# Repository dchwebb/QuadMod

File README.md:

# Quadmod

Quadmod
--------

Quadmod is a Eurorack modular four channel effect module. A modulation section allows either phasing or flanging followed by a delay. As part of the Mountjoy Modular polyphonic range the module uses a series of intermodulation paths to convert a four channel input to a stereo output.

### Phaser
The phaser uses 4 (configurable up to 16) all pass filters to create the phasing effect. Each channel's all pass filter is 45° out of phase with the last. The regeneration (feedback) control progressively mixes one channel to the next to widen the stereo spectrum.

### Flanger
The flanger uses multiple short modulated delays to create a flanger/chorus effect. The delay times are modulated with a 45° phase shift from channel to channel. A wide option (on by default) mixes a further 180° phase shifted version of each channel's signal to the next channel.

Technical
---------

Quadmod uses an STM32563 microcontroller which controls a four channel Audio Codec (AsahiKasei AK4619) using SPI for configuration and SAI (Serial Ausio Interface) peripheral to manage the 4 in and 4 out I2S audio streams. The microcontroller reads the front panel controls with internal 12 bit ADCs.

A USB socket is provided for serial configuration and a web editor using WebSerial provides a UI for editing settings. Three LEDs are controlled with PWM from the MCU to indicate modulation LFO rates and delay times.

Construction is a sandwich of three PCBs with a component board, a controls board and a panel. PCBs designed in Kicad v7.

[Components schematic](https://raw.githubusercontent.com/dchwebb/Quadmod/master/Hardware/Quadmod_Components.pdf)

[Controls schematic](https://raw.githubusercontent.com/dchwebb/Quadmod/master/Hardware/Quadmod_Controls.pdf)

In addition the the Eurorack +/-12V rails (which have polarity protection and filtering) a digital 3.3v rail is supplied using a TI TPS561201 and analog 3.3v is generated with an LM1117-3.3.

Errata
------

Version 1 of the component PCB had microcontroller pins PC0 (SAI2_SD_A) and PC1 (DLY_TIME_POT) flipped.

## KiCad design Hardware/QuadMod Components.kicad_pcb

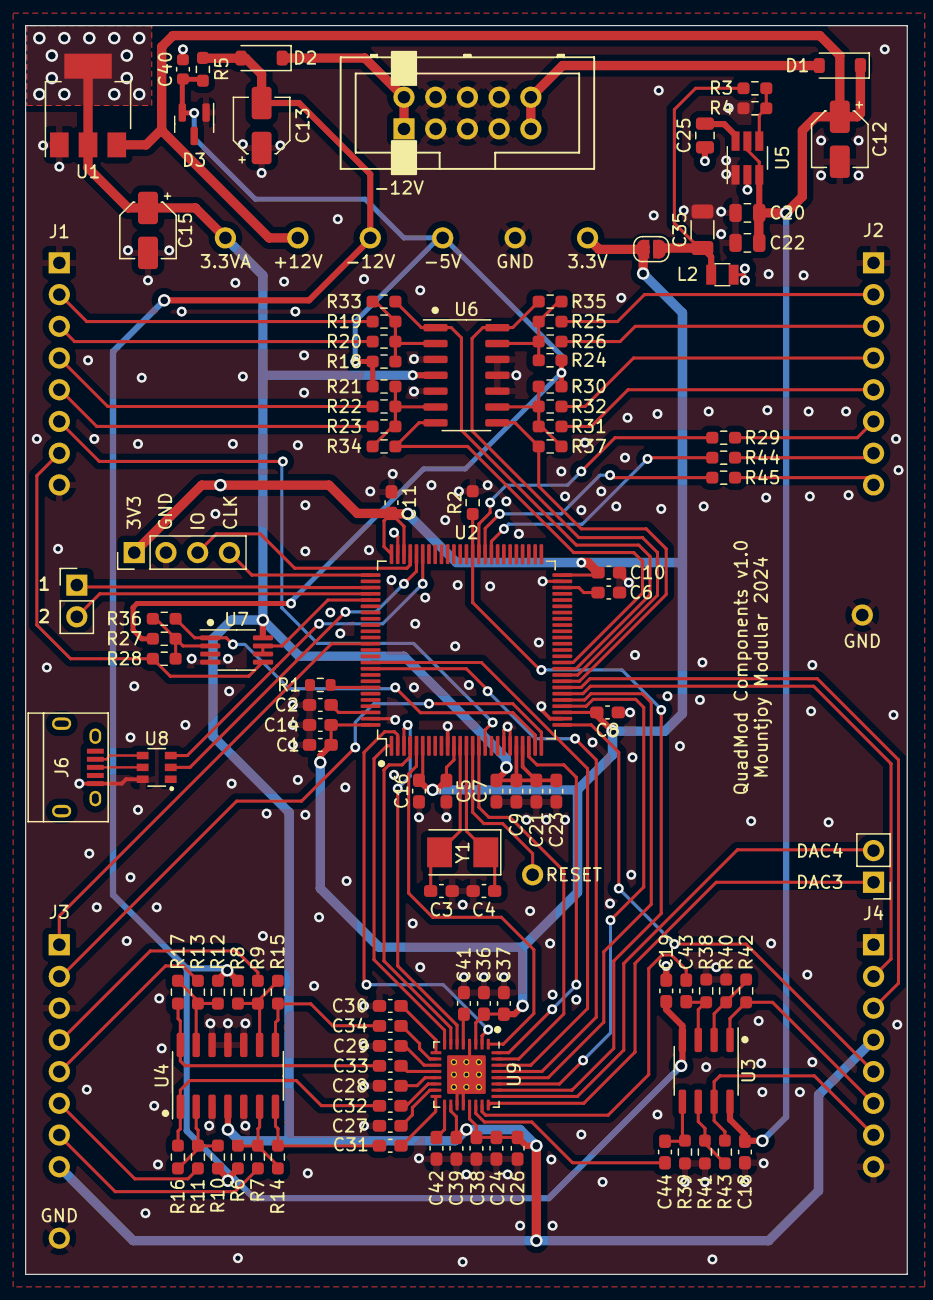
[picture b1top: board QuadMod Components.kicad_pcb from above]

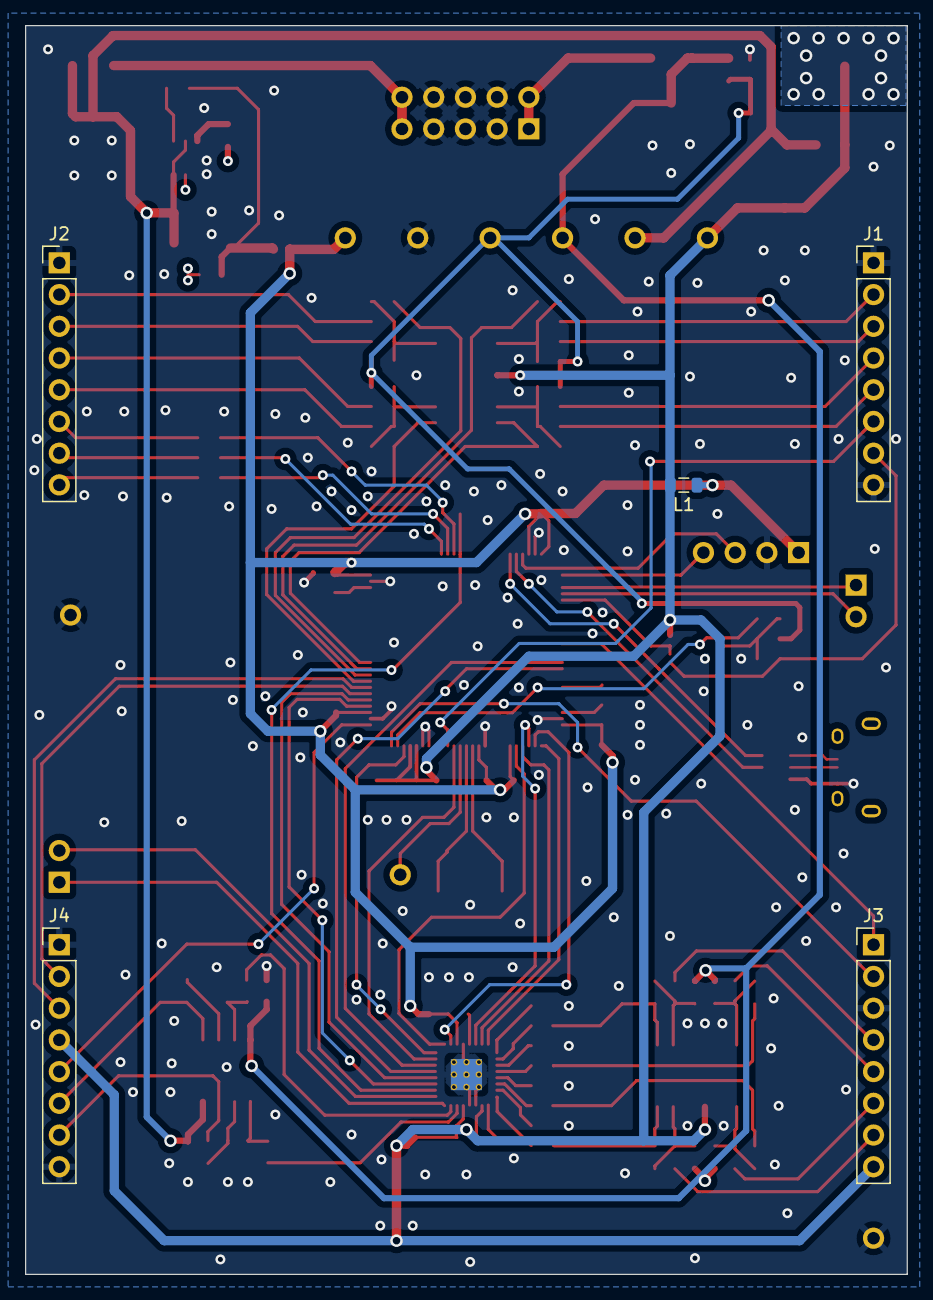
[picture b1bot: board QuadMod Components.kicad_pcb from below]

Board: 4 copper layers, 70.6 x 100.0 mm, 122 parts (5 on the bottom side), 102 nets.

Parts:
C1: 4.7uF; C_0603_1608Metric_Pad1.08x0.95mm_HandSolder
C2, C6, C41, C42: 2.2uF; C_0603_1608Metric_Pad1.08x0.95mm_HandSolder
C3, C4: 30pF; C_0603_1608Metric_Pad1.08x0.95mm_HandSolder
C5, C8, C9, C10, C11, C14, C16, C18, C19, C21, C24, C37, C38: 100nF; C_0603_1608Metric_Pad1.08x0.95mm_HandSolder
C7, C23, C27, C28, C29, C30, C31, C32, C33, C34, C43, C44: 1uF; C_0603_1608Metric_Pad1.08x0.95mm_HandSolder
C12: 47uF; CP_Elec_4x5.8
C13, C15: 22uF; CP_Elec_4x5.8
C20, C22: 10uF; C_0805_2012Metric
C25: 100nF; C_0805_2012Metric
C26, C36, C39: 10uF; C_0603_1608Metric_Pad1.08x0.95mm_HandSolder
C35: 47uF; R_1206_3216Metric
C40: 100nF; C_0603_1608Metric
D1, D2: 1N5819; D_SOD-123
D3: LM4040DBZ-5; SOT-23
J1, J2, J3, J4: Conn_01x08_Pin; PinHeader_1x08_P2.54mm_Vertical
J5: Eurorack_10_pin_power; Eurorack_10_pin_header
J6: USB_B_Micro; USB_Micro-B_Amphenol
J7: Prog_Header; PinHeader_1x04_P2.54mm_Vertical
J8: Extra_Outs; PinHeader_1x02_P2.54mm_Vertical
J9: Test_Outs; PinHeader_1x02_P2.54mm_Vertical
JP2: Jumper; SolderJumper-2_P1.3mm_Open_RoundedPad1.0x1.5mm
L1: L; L_0805_2012Metric
L2: 3.3uH; L_0806
R1: 100k; R_0603_1608Metric
R2, R4, R40, R41: 10k; R_0603_1608Metric_Pad0.98x0.95mm_HandSolder
R3: 33k; R_0603_1608Metric_Pad0.98x0.95mm_HandSolder
R5: 2k2; R_0603_1608Metric_Pad0.98x0.95mm_HandSolder
R6, R8, R10, R12: 100k; R_0603_1608Metric_Pad0.98x0.95mm_HandSolder
R7, R9, R11, R13: 68k; R_0603_1608Metric_Pad0.98x0.95mm_HandSolder
R14, R15, R16, R17, R42, R43: 14k; R_0603_1608Metric_Pad0.98x0.95mm_HandSolder
R18, R21, R24, R27, R30: 75k; R_0603_1608Metric_Pad0.98x0.95mm_HandSolder
R19, R22, R25, R28, R31: 91k; R_0603_1608Metric_Pad0.98x0.95mm_HandSolder
R20, R23, R26, R32, R33, R34, R35, R36, R37: 47k; R_0603_1608Metric_Pad0.98x0.95mm_HandSolder
R29, R44, R45: 1k; R_0603_1608Metric_Pad0.98x0.95mm_HandSolder
R38, R39: 390k; R_0603_1608Metric_Pad0.98x0.95mm_HandSolder
TP1, TP2, TP3, TP4, TP5, TP6, TP7, TP9: TestPoint; 1mm_Test_Point
TP8: Reset; 1mm_Test_Point
U1: LD1117-3.3-4Tab; SOT-223-3_TabPin2
U2: STM32H563VIT; LQFP-100_14x14mm_P0.5mm
U3: TL072; SOIC-8_3.9x4.9mm_P1.27mm
U4, U6: MCP6004; SO-14_3.9x8.65mm_P1.27mm
U5: TPS561201; SOT-23-6_Handsoldering
U7: MCP6002-xSN; MSOP-8_3x3mm_P0.65mm
U8: STF202-22T1G
U9: AK4619VN; QFN-32-1EP_5x5mm_P0.5mm_EP3.1x3.1mm_ThermalVias
Y1: 8MHz 20pF; Crystal_SMD_5032-2Pin_5.0x3.2mm

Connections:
+3.3V: C1.2, C5.2, C8.2, C10.2, C11.2, C14.2, C16.2, C36.2, C37.2, J7.1, JP2.2 (B), L1.1, TP5.1, U2.6 (VBAT), U2.11 (VDD), U2.28 (VDD), U2.50 (VDD), U2.73 (VDDUSB), U2.75 (VDD), U2.100 (VDD), U9.3 (TVDD)
+3.3VA: C7.2, C9.2, C15.1, C21.2, C23.2, C24.2, C26.2, C38.2, C39.2, J3.8, J4.4, L1.2, TP4.1, U1.2 (VO), U2.21 (VREF+), U2.22 (VDDA), U4.4 (V+), U6.4 (V+), U7.8 (V+), U9.18 (AVDD), U9.21 (VREFH)
+12V: C12.1, C18.2, C20.1, C22.1, D1.1 (K), TP2.1, U1.3 (VI), U3.8 (V+), U5.3 (VIN), U5.5 (EN)
-12V: C13.2, C19.2, D2.2 (A), R5.1, R6.2, R8.2, R10.2, R12.2, TP3.1, U3.4 (V-)
/+12V_IN: D1.2 (A), J5.9, J5.10
/-5V_REF: C40.2, D3.2 (A), R5.2, R18.2, R21.2, R24.2, R27.2, R30.2, TP1.1
/-12V_IN: D2.1 (K), J5.1, J5.2
/Audio_In1: C31.2, R14.1, U4.7
/Audio_In2: C32.2, R16.1, U4.1
/Audio_In3: C33.2, R17.1, U4.14
/Audio_In4: C34.2, R15.1, U4.8
/Audio_Out1: C44.2, U9.22 (AOUT1L)
/Audio_Out2: C43.2, U9.23 (AOUT1R)
/Audio_Out3: J8.1, U9.24 (AOUT2L)
/Audio_Out4: J8.2, U9.25 (AOUT2R)
/CB: C25.2, U5.6 (VBST)
/CLOCKED_LED: J2.6, R29.2
/Clock_Scaled: U2.80 (PC12), U7.6 (-), U7.7
/Clocked_Led_Out: R29.1, U2.61 (PD14)
/D3V3: C35.1, JP2.1 (A), L2.2, R3.1
/D+: J6.3 (D+), U8.5 (D1_IN)
/D-: J6.2 (D-), U8.4 (D2_IN)
/DELAY_LED: J2.7, R44.2
/DLY_FEEDBACK: J3.2, U2.25 (PA2)
/DLY_FILTER_CV: J1.4, R22.2
/DLY_FILTER_POT: J1.5, R23.2
/DLY_MIX: J4.3, U2.32 (PA7)
/DLY_TIME_CV: J1.7, R28.2, U7.5 (+)
/DLY_TIME_POT: J1.6, U2.16 (PC1)
/Delay_Filter: R34.1, U2.36 (PB1), U6.7
/Delay_Led_Out: R44.1, U2.59 (PD12)
/Delay_Time: R36.1, U2.24 (PA1), U7.1
/FB: R3.2, R4.1, U5.4 (VFB)
/FX_FEEDBACK_CV: J2.2, R25.2
/FX_FEEDBACK_POT: J2.3, R26.2
/FX_Feedback: R35.1, U2.34 (PC5), U6.14
/FX_LED: J2.8, R45.2
/FX_Led_Out: R45.1, U2.60 (PD13)
/FX_MIX: J4.5, U2.26 (PA3)
/FX_TYPE: J3.1, U2.87 (PD6)
/IN1: J3.7, R7.2
/IN2: J3.6, R11.2
/IN3: J3.5, R13.2
/IN4: J3.4, R9.2
/LFO_BASEFREQ_CV: J1.2, R19.2
/LFO_BASEFREQ_POT: J1.3, R20.2
/LFO_Base_Freq: R33.1, U2.35 (PB0), U6.1
/LFO_RANGE: J4.2, U2.31 (PA6)
/LFO_SPEED_CV: J2.5, R31.2
/LFO_SPEED_POT: J2.4, R32.2
/LFO_Speed: R37.1, U2.33 (PC4), U6.8
/OUT_AMP1: J4.7, R43.1, U3.7
/OUT_AMP2: J4.6, R42.1, U3.1
/PDN: R2.1, U2.62 (PD15), U9.26 (PDN)
/SAI1_FS_A: U2.3 (PE4), U9.6 (LRCK)
/SAI1_MCLK_A: U2.1 (PE2), U9.8 (MCLK)
/SAI1_SCK_A: U2.4 (PE5), U9.7 (BICK)
/SAI1_SD_A: U2.5 (PE6), U9.1 (SDIN1)
/SAI1_SD_B: U2.2 (PE3), U9.2 (SDIN2)
/SAI2_SD_A: U2.15 (PC0), U9.31 (SDOUT1)
/SAI2_SD_B: U2.23 (PA0), U9.32 (SDOUT2)
/SPI1_MISO: U2.90 (PB4), U9.30 (SDA/SO)
/SPI1_MOSI: U2.91 (PB5), U9.29 (SI)
/SPI1_NSS: U2.29 (PA4), U9.27 (CAD/~CS)
/SPI1_SCK: U2.30 (PA5), U9.28 (SCL/SCLK)
/SWCLK: J7.4, U2.76 (PA14)
/SWIO: J7.3, U2.72 (PA13)
/Test_Out1: J9.1, U2.78 (PC10)
/Test_Out2: J9.2, U2.79 (PC11)
/USB_DM: U2.70 (PA11), U8.3 (D2_OUT)
/USB_DP: U2.71 (PA12), U8.2 (D1_OUT)
/VSW: C25.1, L2.1, U5.2 (SW)
GND: C1.1, C2.2, C3.2, C4.2, C5.1, C6.2, C7.1, C8.1, C9.1, C10.1, C11.1, C12.2, C13.1, C14.1, C15.2, C16.1, C18.1, C19.1, C20.2, C21.1, C22.2, C23.1, C24.1, C26.1, C27.2, C28.2, C29.2, C30.2, C35.2, C36.1, C37.1, C38.1, C39.1, C40.1, C41.2, C42.2, D3.1 (K), J1.1, J1.8, J2.1, J3.3, J4.1, J4.8, J5.3, J5.4, J5.5, J5.6, J5.7, J5.8, J6.5 (GND), J7.2, R1.1, R2.2, R4.2, R38.2, R39.2, R40.2, R41.2, TP6.1, TP7.1, TP9.1, U1.1 (GND), U2.10 (VSS), U2.19 (VSSA), U2.20 (VREF-), U2.27 (VSS), U2.49 (VSS), U2.74 (VSS), U2.99 (VSS), U4.3 (+), U4.5 (+), U4.10 (+), U4.11 (V-), U4.12 (+), U5.1 (GND), U6.3 (+), U6.5 (+), U6.10 (+), U6.11 (V-), U6.12 (+), U7.3 (+), U7.4 (V-), U8.6 (GND), U9.4 (VSS2), U9.19 (VSS1), U9.20 (VREFL), U9.33 (PAD)
unnamed: C2.1, U2.98 (VCAP)
unnamed: C6.1, U2.48 (VCAP)
unnamed: R1.2, U2.94 (BOOT0)
unnamed: TP8.1, U2.14 (NRST)
unnamed: C3.1, U2.12 (PH0), Y1.2
unnamed: C4.1, U2.13 (PH1), Y1.1
unnamed: C43.1, R38.1, U3.3 (+)
unnamed: R40.1, R42.2, U3.2 (-)
unnamed: C44.1, R39.1, U3.5 (+)
unnamed: R41.1, R43.2, U3.6 (-)
unnamed: R10.1, R11.1, R16.2, U4.2 (-)
unnamed: R6.1, R7.1, R14.2, U4.6 (-)
unnamed: R8.1, R9.1, R15.2, U4.9 (-)
unnamed: R12.1, R13.1, R17.2, U4.13 (-)
unnamed: R18.1, R19.1, R20.1, R33.2, U6.2 (-)
unnamed: R21.1, R22.1, R23.1, R34.2, U6.6 (-)
unnamed: R30.1, R31.1, R32.1, R37.2, U6.9 (-)
unnamed: R24.1, R25.1, R26.1, R35.2, U6.13 (-)
unnamed: R27.1, R28.1, R36.2, U7.2 (-)
unnamed: C41.1, U9.5 (AVDRV)
unnamed: C27.1, U9.15 (IN1N/AIN2L/GND3L)
unnamed: C31.1, U9.16 (IN1P/AIN1L/AIN3L)
unnamed: C28.1, U9.13 (IN2N/AIN2R/GND3R)
unnamed: C32.1, U9.14 (IN2P/AIN1R/AIN3R)
unnamed: C29.1, U9.11 (IN3N/AIN5L/GND6L)
unnamed: C33.1, U9.12 (IN3P/AIN4L/AIN6L)
unnamed: C30.1, U9.9 (IN4N/AIN5R/GND6R)
unnamed: C34.1, U9.10 (IN4P/AIN4R/AIN6R)
unnamed: C42.1, U9.17 (VCOM)

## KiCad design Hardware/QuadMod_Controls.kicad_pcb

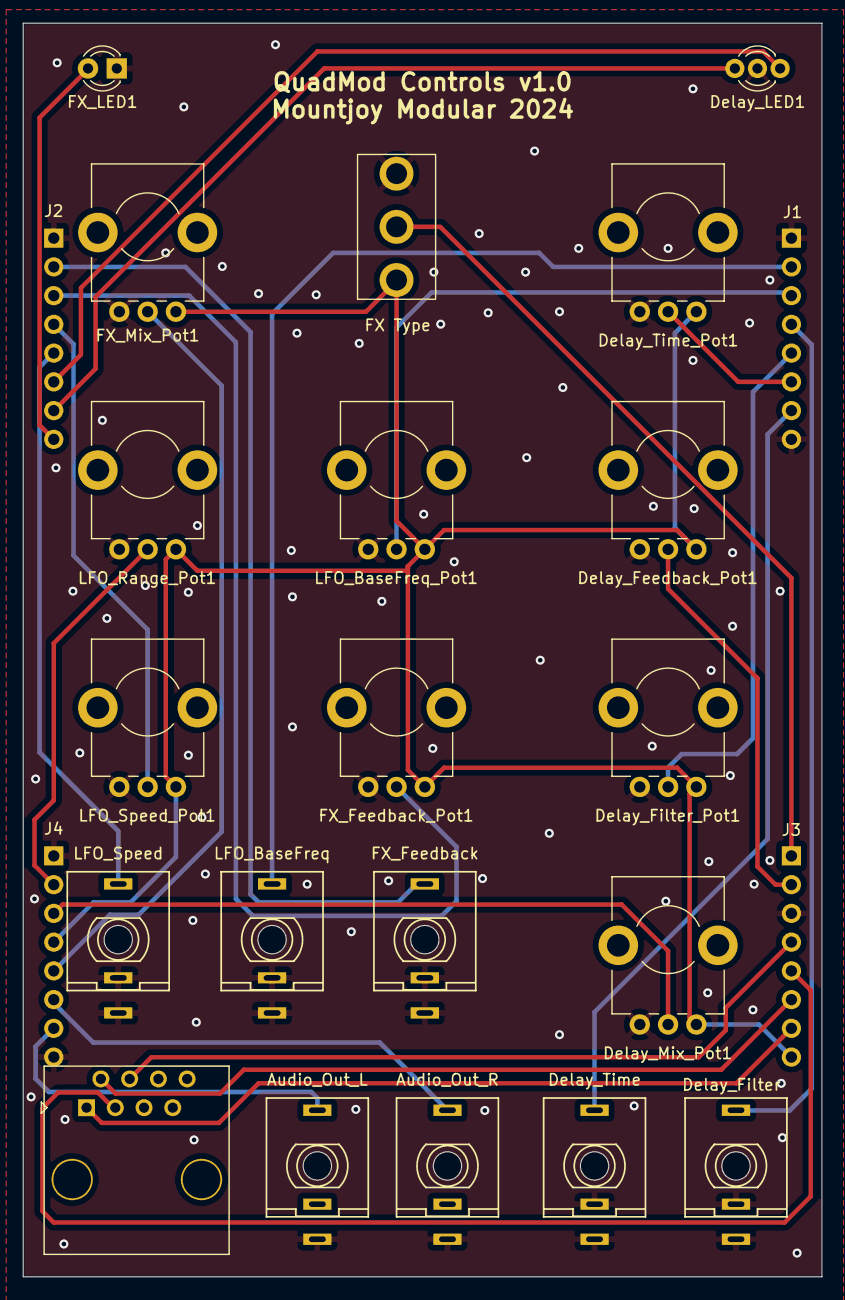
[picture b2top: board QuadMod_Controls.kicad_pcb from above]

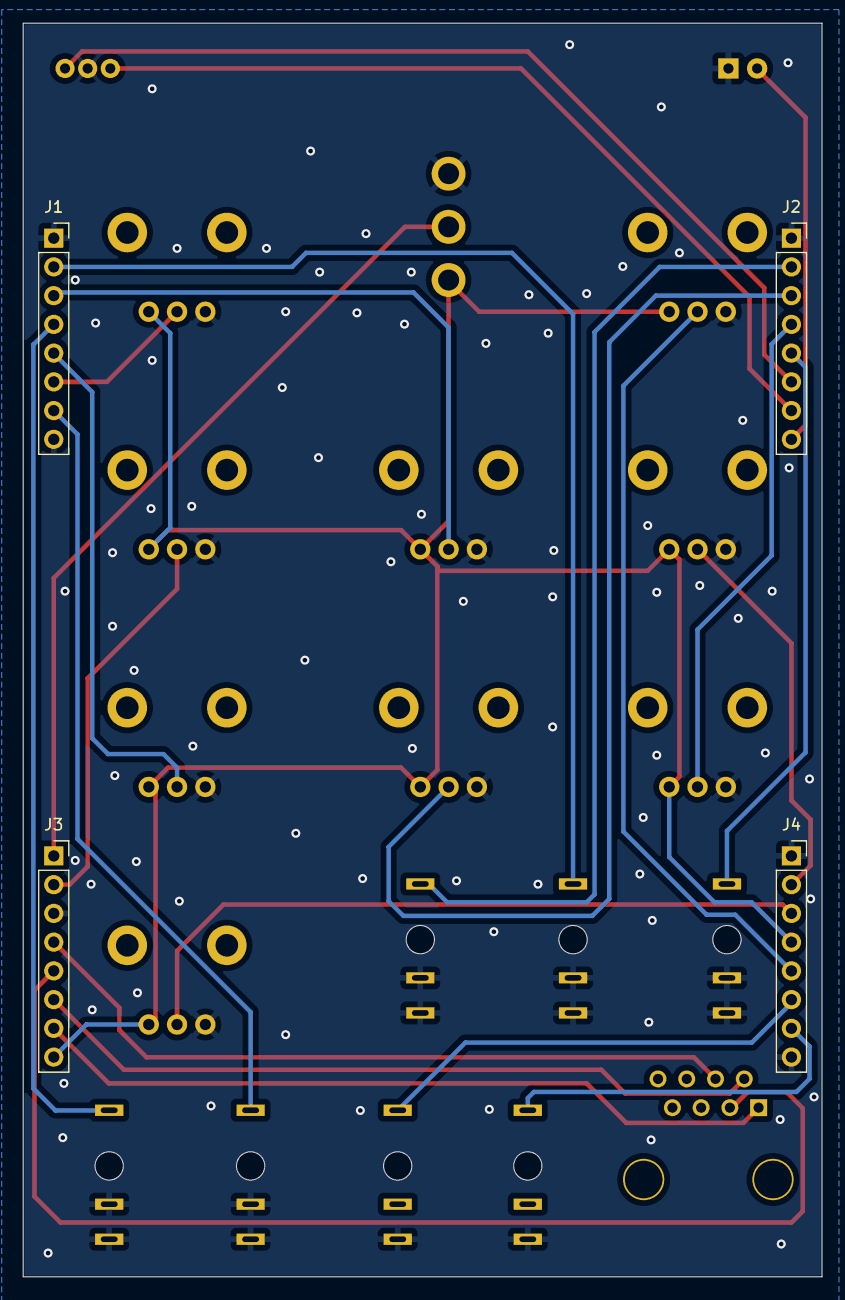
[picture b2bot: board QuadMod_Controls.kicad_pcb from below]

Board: 2 copper layers, 70.6 x 110.8 mm, 25 parts (4 on the bottom side), 26 nets.

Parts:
Delay_Feedback_Pot1: B10k; Alpha_9mm_Potentiometer_Aligned
Delay_Filter_Pot1: B10k; Alpha_9mm_Potentiometer_Aligned
Delay_LED1: LED_Dual_AKA; LED_D3.0mm-3
Delay_Mix_Pot1: B10k; Alpha_9mm_Potentiometer_Aligned
Delay_Time_Pot1: B10k; Alpha_9mm_Potentiometer_Aligned
FX_Feedback_Pot1: B10k; Alpha_9mm_Potentiometer_Aligned
FX_LED1: LED; LED_D3.0mm
FX_Mix_Pot1: B10k; Alpha_9mm_Potentiometer_Aligned
J1, J2, J3, J4: Conn_01x08_Pin; PinSocket_1x08_P2.54mm_Vertical
J5: Delay_Time; THONKICONN_hole
J6: Delay_Filter; THONKICONN_hole
J7: LFO_BaseFreq; THONKICONN_hole
J8: FX_Feedback; THONKICONN_hole
J9: LFO_Speed; THONKICONN_hole
J10: Audio_Out_L; THONKICONN_hole
J11: Audio_Out_R; THONKICONN_hole
J13: Audio_In; RJ45_Molex_42878-8506
LFO_BaseFreq_Pot1: B10k; Alpha_9mm_Potentiometer_Aligned
LFO_Range_Pot1: B10k; Alpha_9mm_Potentiometer_Aligned
LFO_Speed_Pot1: B10k; Alpha_9mm_Potentiometer_Aligned
PANEL: Panel; 3D_Dummy
SW1: FX_Type_Switch; SPDT_Miniature

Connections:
+3.3VA: Delay_Feedback_Pot1.1, Delay_Filter_Pot1.1, Delay_Mix_Pot1.1, Delay_Time_Pot1.1, FX_Feedback_Pot1.1, FX_Mix_Pot1.1, J3.8, J4.4, LFO_BaseFreq_Pot1.1, LFO_Range_Pot1.1, LFO_Speed_Pot1.1, SW1.1 (A)
/CLOCKED_LED: Delay_LED1.1 (A1), J2.6
/DELAY_LED: Delay_LED1.3 (A2), J2.7
/DLY_FEEDBACK: Delay_Feedback_Pot1.2, J3.2
/DLY_FILTER_CV: J1.4, J6.3
/DLY_FILTER_POT: Delay_Filter_Pot1.2, J1.5
/DLY_MIX: Delay_Mix_Pot1.2, J4.3
/DLY_TIME_CV: J1.7, J5.3
/DLY_TIME_POT: Delay_Time_Pot1.2, J1.6
/FX_FEEDBACK_CV: J2.2, J8.3
/FX_FEEDBACK_POT: FX_Feedback_Pot1.2, J2.3
/FX_LED: FX_LED1.2 (A), J2.8
/FX_MIX: FX_Mix_Pot1.2, J4.5
/FX_TYPE: J3.1, SW1.2 (B)
/IN1: J3.7, J13.1
/IN2: J3.6, J13.2
/IN3: J3.5, J13.3
/IN4: J3.4, J13.4
/LFO_BASEFREQ_CV: J1.2, J7.3
/LFO_BASEFREQ_POT: J1.3, LFO_BaseFreq_Pot1.2
/LFO_RANGE: J4.2, LFO_Range_Pot1.2
/LFO_SPEED_CV: J2.5, J9.3
/LFO_SPEED_POT: J2.4, LFO_Speed_Pot1.2
/OUT_AMP1: J4.7, J10.3
/OUT_AMP2: J4.6, J11.3
GND: Delay_Feedback_Pot1.3, Delay_Filter_Pot1.3, Delay_LED1.2 (K), Delay_Mix_Pot1.3, Delay_Time_Pot1.3, FX_Feedback_Pot1.3, FX_LED1.1 (K), FX_Mix_Pot1.3, J1.1, J1.8, J2.1, J3.3, J4.1, J4.8, J5.1, J5.2, J6.1, J6.2, J7.1, J7.2, J8.1, J8.2, J9.1, J9.2, J10.1, J11.1, LFO_BaseFreq_Pot1.3, LFO_Range_Pot1.3, LFO_Speed_Pot1.3, SW1.3 (C)

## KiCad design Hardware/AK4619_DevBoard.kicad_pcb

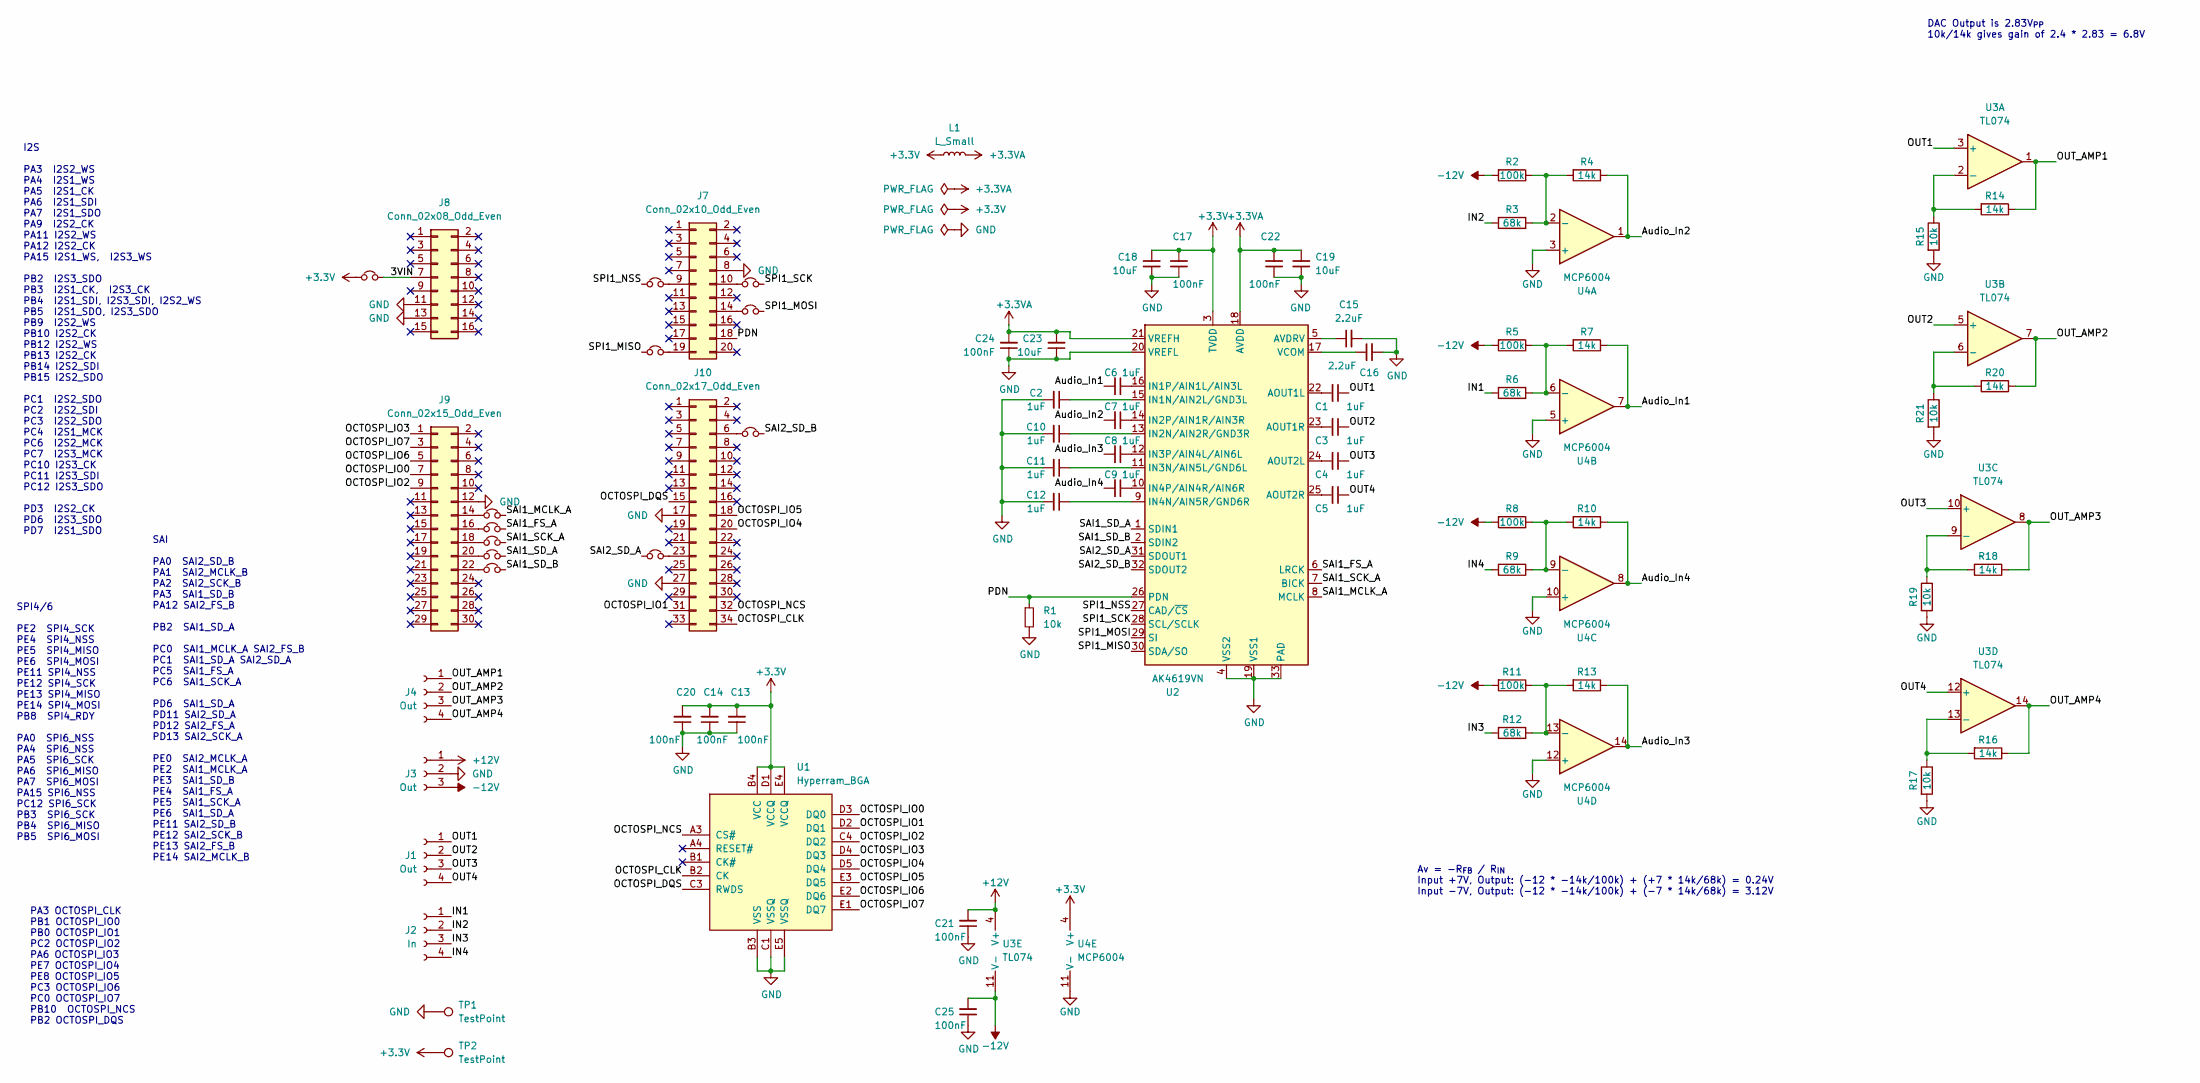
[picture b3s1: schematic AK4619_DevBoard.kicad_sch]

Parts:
C1, C2, C3, C4, C5, C6, C7, C8, C9, C10, C11, C12: 1uF; C_0603_1608Metric_Pad1.08x0.95mm_HandSolder
C13, C14, C17, C20, C21, C22, C24, C25: 100nF; C_0603_1608Metric_Pad1.08x0.95mm_HandSolder
C15, C16: 2.2uF; C_0603_1608Metric_Pad1.08x0.95mm_HandSolder
C18, C19, C23: 10uF; C_0603_1608Metric_Pad1.08x0.95mm_HandSolder
J1, J4: Out; PinSocket_1x04_P2.54mm_Vertical
J2: In; PinSocket_1x04_P2.54mm_Vertical
J3: Out; PinSocket_1x03_P2.54mm_Vertical
J7: Conn_02x10_Odd_Even; PinHeader_2x10_P2.54mm_Vertical
J8: Conn_02x08_Odd_Even; PinHeader_2x08_P2.54mm_Vertical
J9: Conn_02x15_Odd_Even; PinHeader_2x15_P2.54mm_Vertical
J10: Conn_02x17_Odd_Even; PinHeader_2x17_P2.54mm_Vertical
JP1, JP2, JP3, JP4, JP5, JP6, JP7, JP8, JP9, JP10, JP11, JP12: Jumper_NC_Small; SolderJumper-2_P1.3mm_Bridged_RoundedPad1.0x1.5mm
L1: L_Small; L_0603_1608Metric_Pad1.05x0.95mm_HandSolder
R1: 10k; R_0603_1608Metric_Pad0.98x0.95mm_HandSolder
R2, R5, R8, R11: 100k; R_0603_1608Metric_Pad0.98x0.95mm_HandSolder; Part_Number C4184
R3, R6, R9, R12: 68k; R_0603_1608Metric_Pad0.98x0.95mm_HandSolder; Part_Number C25819
R4, R7, R10, R13, R14, R16, R18, R20: 14k; R_0603_1608Metric_Pad0.98x0.95mm_HandSolder; Part_Number C23212
R15, R17, R19, R21: 10k; R_0603_1608Metric_Pad0.98x0.95mm_HandSolder; Part_Number C23212
TP1, TP2: TestPoint; 1mm_Test_Point
U1: Hyperram_BGA; BGA-24_5x5_6.0x8.0mm
U2: AK4619VN; QFN-32-1EP_5x5mm_P0.5mm_EP3.1x3.1mm_ThermalVias
U3: TL074; SO-14_3.9x8.65mm_P1.27mm
U4: MCP6004; SO-14_3.9x8.65mm_P1.27mm

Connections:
+3.3V: C13.2, C14.2, C17.2, C18.2, C20.2, JP12.1, L1.1, TP2.1, U1.B4 (VCC), U1.D1 (VCCQ), U1.E4 (VCCQ), U2.3 (TVDD), U4.4 (V+)
+3.3VA: C19.2, C22.2, C23.2, C24.2, L1.2, U2.18 (AVDD), U2.21 (VREFH)
+12V: C21.2, J3.1, U3.4 (V+)
-12V: C25.2, J3.3, R2.2, R5.2, R8.2, R11.2, U3.11 (V-)
/3VIN: J8.7, JP12.2
/Audio_In1: C6.2, R7.1, U4.7
/Audio_In2: C7.2, R4.1, U4.1
/Audio_In3: C8.2, R13.1, U4.14
/Audio_In4: C9.2, R10.1, U4.8
/IN1: J2.1, R6.2
/IN2: J2.2, R3.2
/IN3: J2.3, R12.2
/IN4: J2.4, R9.2
/OCTOSPI_CLK: J10.34, U1.B2 (CK)
/OCTOSPI_DQS: J10.15, U1.C3 (RWDS)
/OCTOSPI_IO0: J9.7, U1.D3 (DQ0)
/OCTOSPI_IO1: J10.31, U1.D2 (DQ1)
/OCTOSPI_IO2: J9.9, U1.C4 (DQ2)
/OCTOSPI_IO3: J9.1, U1.D4 (DQ3)
/OCTOSPI_IO4: J10.20, U1.D5 (DQ4)
/OCTOSPI_IO5: J10.18, U1.E3 (DQ5)
/OCTOSPI_IO6: J9.5, U1.E2 (DQ6)
/OCTOSPI_IO7: J9.3, U1.E1 (DQ7)
/OCTOSPI_NCS: J10.32, U1.A3 (CS#)
/OUT1: C1.1, J1.1, U3.3 (+)
/OUT2: C3.1, J1.2, U3.5 (+)
/OUT3: C4.1, J1.3, U3.10 (+)
/OUT4: C5.1, J1.4, U3.12 (+)
/OUT_AMP1: J4.1, R14.1, U3.1
/OUT_AMP2: J4.2, R20.1, U3.7
/OUT_AMP3: J4.3, R18.1, U3.8
/OUT_AMP4: J4.4, R16.1, U3.14
/PDN: J7.18, R1.1, U2.26 (PDN)
/SAI1_FS_A: JP10.2, U2.6 (LRCK)
/SAI1_MCLK_A: JP11.2, U2.8 (MCLK)
/SAI1_SCK_A: JP9.2, U2.7 (BICK)
/SAI1_SD_A: JP8.2, U2.1 (SDIN1)
/SAI1_SD_B: JP7.2, U2.2 (SDIN2)
/SAI2_SD_A: JP6.1, U2.31 (SDOUT1)
/SAI2_SD_B: JP5.2, U2.32 (SDOUT2)
/SPI1_MISO: JP4.1, U2.30 (SDA/SO)
/SPI1_MOSI: JP1.2, U2.29 (SI)
/SPI1_NSS: JP2.1, U2.27 (CAD/~CS)
/SPI1_SCK: JP3.2, U2.28 (SCL/SCLK)
GND: C2.2, C10.2, C11.2, C12.2, C13.1, C14.1, C15.2, C16.2, C17.1, C18.1, C19.1, C20.1, C21.1, C22.1, C23.1, C24.1, C25.1, J3.2, J7.8, J8.11, J8.13, J9.12, J10.17, J10.27, R1.2, R15.2, R17.2, R19.2, R21.2, TP1.1, U1.B3 (VSS), U1.C1 (VSSQ), U1.E5 (VSSQ), U2.4 (VSS2), U2.19 (VSS1), U2.20 (VREFL), U2.33 (PAD), U4.3 (+), U4.5 (+), U4.10 (+), U4.11 (V-), U4.12 (+)
unnamed: J7.9, JP2.2
unnamed: J7.10, JP3.1
unnamed: J7.14, JP1.1
unnamed: J7.19, JP4.2
unnamed: J9.14, JP11.1
unnamed: J9.16, JP10.1
unnamed: J9.18, JP9.1
unnamed: J9.20, JP8.1
unnamed: J9.22, JP7.1
unnamed: J10.6, JP5.1
unnamed: J10.23, JP6.2
unnamed: C1.2, U2.22 (AOUT1L)
unnamed: C3.2, U2.23 (AOUT1R)
unnamed: C4.2, U2.24 (AOUT2L)
unnamed: C5.2, U2.25 (AOUT2R)
unnamed: C15.1, U2.5 (AVDRV)
unnamed: C2.1, U2.15 (IN1N/AIN2L/GND3L)
unnamed: C6.1, U2.16 (IN1P/AIN1L/AIN3L)
unnamed: C10.1, U2.13 (IN2N/AIN2R/GND3R)
unnamed: C7.1, U2.14 (IN2P/AIN1R/AIN3R)
unnamed: C11.1, U2.11 (IN3N/AIN5L/GND6L)
unnamed: C8.1, U2.12 (IN3P/AIN4L/AIN6L)
unnamed: C12.1, U2.9 (IN4N/AIN5R/GND6R)
unnamed: C9.1, U2.10 (IN4P/AIN4R/AIN6R)
unnamed: C16.1, U2.17 (VCOM)
unnamed: R14.2, R15.1, U3.2 (-)
unnamed: R20.2, R21.1, U3.6 (-)
unnamed: R18.2, R19.1, U3.9 (-)
unnamed: R16.2, R17.1, U3.13 (-)
unnamed: R2.1, R3.1, R4.2, U4.2 (-)
unnamed: R5.1, R6.1, R7.2, U4.6 (-)
unnamed: R8.1, R9.1, R10.2, U4.9 (-)
unnamed: R11.1, R12.1, R13.2, U4.13 (-)

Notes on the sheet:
PA3 OCTOSPI_CLK PB1 OCTOSPI_IO0 PB0 OCTOSPI_IO1 PC2 OCTOSPI_IO2 PA6 OCTOSPI_IO3 PE7 OCTOSPI_IO4 PE8 OCTOSPI_IO5 PC3 OCTOSPI_IO6 PC0 OCTOSPI_IO7 PB10 OCTOSPI_NCS PB2 OCTOSPI_DQS
I2S PA3 I2S2_WS PA4 I2S1_WS PA5 I2S1_CK PA6 I2S1_SDI PA7 I2S1_SDO PA9 I2S2_CK PA11 I2S2_WS PA12 I2S2_CK PA15 I2S1_WS, I2S3_WS PB2 I2S3_SDO PB3 I2S1_CK, I2S3_CK PB4 I2S1_SDI, I2S3_SDI, I2S2_WS PB5 I2S1_SDO, I2S3_SDO PB9 I2S2_WS PB10 I2S2_CK PB12 I2S2_WS PB13 I2S2_CK PB14 I2S2_SDI PB15 I2S2_SDO PC1 I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
Av = -R_{FB} / R_{IN} Input +7V, Output: (-12 * -14k/100k) + (+7 * 14k/68k) = 0.24V Input -7V, Output: (-12 * -14k/100k) + (-7 * 14k/68k) = 3.12V
SAI PA0 SAI2_SD_B PA1 SAI2_MCLK_B PA2 SAI2_SCK_B PA3 SAI1_SD_B PA12 SAI2_FS_B PB2 SAI1_SD_A PC0 SAI1_MCLK_A SAI2_FS_B PC1 SAI1_SD_A SAI2_SD_A PC5 SAI1_FS_A PC6 SAI1_SCK_A PD6 SAI1_SD_A PD11 SAI2_SD_A PD12 SAI2_FS_A PD13 SAI2_SCK_A PE0 SAI2_MCLK_A PE2 SAI1_MCLK_A PE3 SAI1_SD_B PE4 SAI1_FS_A PE5 SAI1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
SPI4/6 PE2 SPI4_SCK PE4 SPI4_NSS PE5 SPI4_MISO PE6 SPI4_MOSI PE11 SPI4_NSS PE12 SPI4_SCK PE13 SPI4_MISO PE14 SPI4_MOSI PB8 SPI4_RDY PA0 SPI6_NSS PA4 SPI6_NSS PA5 SPI6_SCK PA6 SPI6_MISO PA7 SPI6_MOSI PA15 SPI6_NSS PC12 SPI6_SCK PB3 SPI6_SCK PB4 SPI6_MISO PB5 SPI6_MOSI
DAC Output is 2.83V_{PP} 10k/14k gives gain of 2.4 * 2.83 = 6.8V

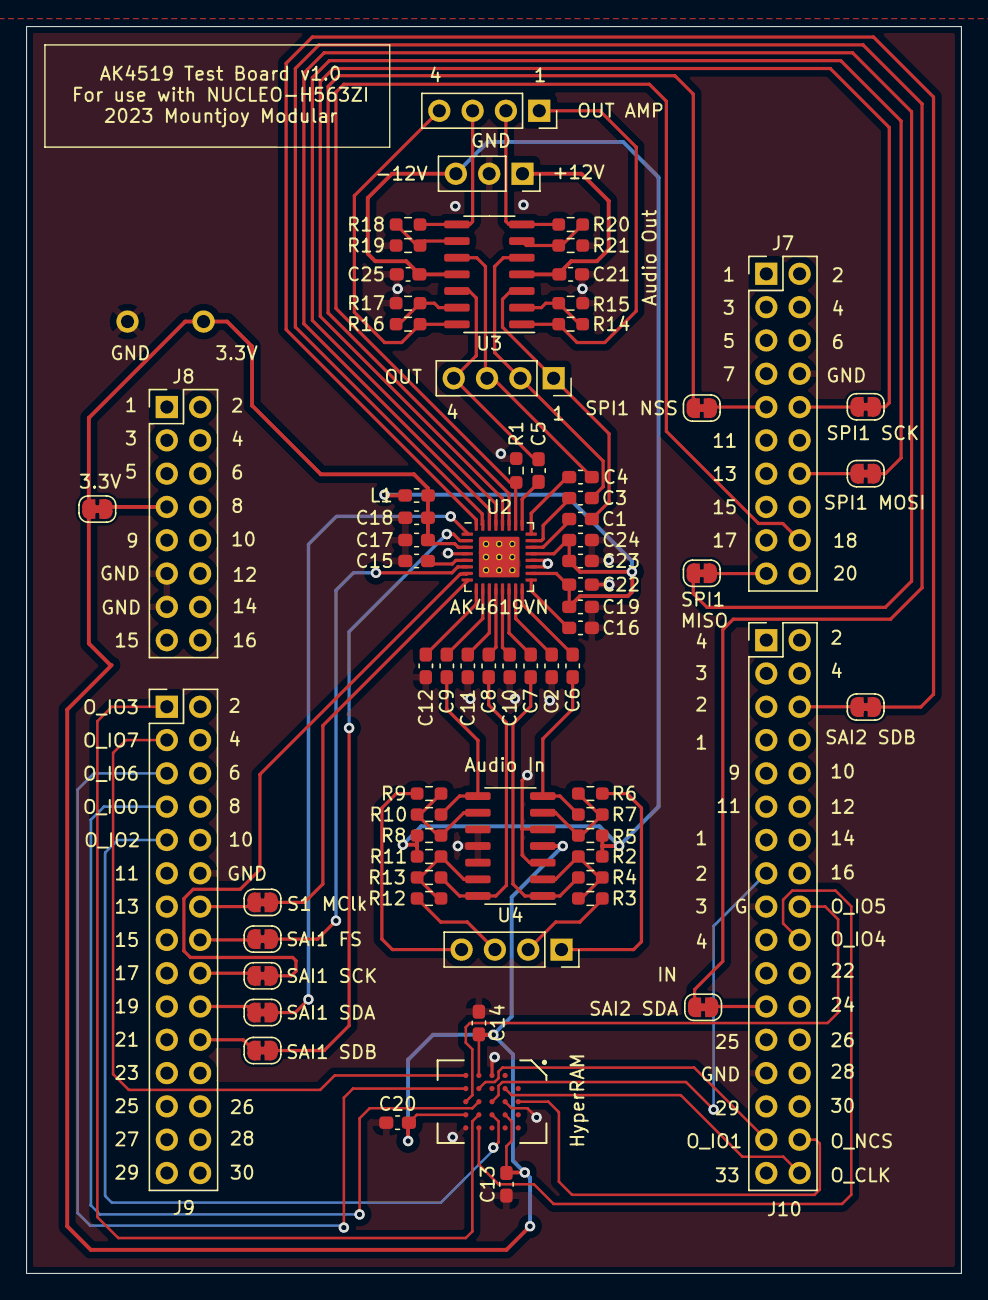
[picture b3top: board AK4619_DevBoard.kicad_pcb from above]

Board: 2 copper layers, 71.3 x 95.1 mm, 73 parts (0 on the bottom side), 78 nets.

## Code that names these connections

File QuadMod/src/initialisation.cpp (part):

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	// Enable SPI
	RCC->APB2ENR |= RCC_APB2ENR_SPI1EN;					// SPI1 clock enable

	GpioPin::Init(GPIOA, 5, GpioPin::Type::AlternateFunction, 5);	// PA5: SPI1_SCK
	GpioPin::Init(GPIOB, 4, GpioPin::Type::AlternateFunction, 5);	// PB4: SPI1_MISO
	GpioPin::Init(GPIOB, 5, GpioPin::Type::AlternateFunction, 5);	// PB5: SPI1_MOSI
	GpioPin::Init(GPIOA, 4, GpioPin::Type::AlternateFunction, 5);	// PA4: SPI1_NSS

	// Configure SPI
	SPI1->CFG1 |= SPI_CFG1_MBR_1;						// Baud rate (100Mhz/x): 000: /2; 001: /4; *010: /8; 011: /16; 100: /32; 101: /64
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	RCC->APB2ENR |= RCC_APB2ENR_SAI2EN;
	RCC->CCIPR5 |= RCC_CCIPR5_SAI1SEL_0;				// SAI Clock Source: 000: pll1_q_ck; *001: pll2_p_ck; 010: pll3_p_ck; 011: AUDIOCLK; 100: per_ck

	GpioPin::Init(GPIOE, 2, GpioPin::Type::AlternateFunction, 6); 	// PE2 SAI1_MCLK_A  AF6
	GpioPin::Init(GPIOE, 3, GpioPin::Type::AlternateFunction, 6); 	// PE3 SAI1_SD_B    AF6
	GpioPin::Init(GPIOE, 4, GpioPin::Type::AlternateFunction, 6); 	// PE4 SAI1_FS_A    AF6
	GpioPin::Init(GPIOE, 5, GpioPin::Type::AlternateFunction, 6); 	// PE5 SAI1_SCK_A   AF6
	GpioPin::Init(GPIOE, 6, GpioPin::Type::AlternateFunction, 6); 	// PE6 SAI1_SD_A    AF6
	GpioPin::Init(GPIOC, 1, GpioPin::Type::AlternateFunction, 8);	// PC1 SAI2_SD_A    AF8
	GpioPin::Init(GPIOA, 0, GpioPin::Type::AlternateFunction, 10);	// PA0 SAI2_SD_B    AF10

	SAI1_Block_A->CR1 |= SAI_xCR1_DS;					// 110: 24 bits; 111: 32 bits
	SAI1_Block_A->CR1 |= SAI_xCR1_CKSTR;				// 0: Signals generated by SAI change on rising edge, signals received by SAI sampled on falling edge; 	1: Signals generated by SAI change on falling edge, signals received sampled on rising edge.
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
	/*--------------------------------------------------------------------------------------------
	Configure ADC Channels to be converted:
	PA3 ADC12_INP15	FX Mix
	PA6 ADC12_INP3	FX LFO Range
	PC4	ADC12_INP4	FX LFO Speed
	PB0	ADC12_INP9	FX LFO Base Frequency
	PC5 ADC12_INP8	FX Regen
	PC0 ADC12_INP10	Delay Time Pot
	PA1 ADC12_INP1	Delay Clock/Time CV
	PA2 ADC12_INP14	Delay Feedback
	PB1 ADC12_IN5   Delay Filter
	PA7 ADC12_INP7	Delay Mix
	*/
	InitAdcPins(ADC2, {15, 3, 4, 9, 8, 10, 1, 14, 5, 7});

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	// TIM4: Used for LED PWM
	RCC->APB1LENR |= RCC_APB1LENR_TIM4EN;

	GpioPin::Init(GPIOD, 12, GpioPin::Type::AlternateFunction, 2);	// PD12 TIM4_CH1 (AF2)
	GpioPin::Init(GPIOD, 13, GpioPin::Type::AlternateFunction, 2);	// PD13 TIM4_CH2 (AF2)
	GpioPin::Init(GPIOD, 14, GpioPin::Type::AlternateFunction, 2);	// PD14 TIM4_CH3 (AF2)

	TIM4->CCMR1 |= TIM_CCMR1_OC1PE;					// Output compare 1 preload enable
	TIM4->CCMR1 |= TIM_CCMR1_OC2PE;					// Output compare 2 preload enable
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
void InitDAC()
{
	// Configure 4 DAC outputs PA4 and PA5 are regular DAC1 buffered outputs; PA2 and PB1 are DAC3 via OpAmp1 and OpAmp3 (Manual p.782)
	RCC->AHB2ENR |= RCC_AHB2ENR_DAC1EN;				// Enable DAC Clock

	DAC1->MCR &= ~DAC_MCR_MODE1_Msk;				// Set to normal mode: DAC1 channel1 is connected to external pin with Buffer enabled
	DAC1->CR |= DAC_CR_EN1;							// Enable DAC using PA4 (DAC_OUT1)

//	DAC1->MCR &= ~DAC_MCR_MODE2_Msk;				// Set to normal mode: DAC1 channel2 is connected to external pin with Buffer enabled
//	DAC1->CR |= DAC_CR_EN2;							// Enable DAC using PA5 (DAC_OUT2)
}


void InitHyperRAM()
{
	// Cypress S27KL0641 DABHI020: 3.0v, 64Mb, 100MHz
	GpioPin::Init(GPIOA, 3, GpioPin::Type::AlternateFunction, 3, GpioPin::DriveStrength::VeryHigh);		// PA3  OCTOSPI_CLK AF3
	GpioPin::Init(GPIOB, 1, GpioPin::Type::AlternateFunction, 6, GpioPin::DriveStrength::VeryHigh);		// PB1  OCTOSPI_IO0 AF6
	GpioPin::Init(GPIOB, 0, GpioPin::Type::AlternateFunction, 6, GpioPin::DriveStrength::VeryHigh);		// PB0  OCTOSPI_IO1 AF6
	GpioPin::Init(GPIOC, 2, GpioPin::Type::AlternateFunction, 9, GpioPin::DriveStrength::VeryHigh);		// PC2  OCTOSPI_IO2 AF9
	GpioPin::Init(GPIOA, 6, GpioPin::Type::AlternateFunction, 6, GpioPin::DriveStrength::VeryHigh);		// PA6  OCTOSPI_IO3 AF6
	GpioPin::Init(GPIOE, 7, GpioPin::Type::AlternateFunction, 10, GpioPin::DriveStrength::VeryHigh); 	// PE7  OCTOSPI_IO4 AF10
	GpioPin::Init(GPIOE, 8, GpioPin::Type::AlternateFunction, 10, GpioPin::DriveStrength::VeryHigh); 	// PE8  OCTOSPI_IO5 AF10
	GpioPin::Init(GPIOC, 3, GpioPin::Type::AlternateFunction, 6, GpioPin::DriveStrength::VeryHigh);		// PC3  OCTOSPI_IO6 AF6
	GpioPin::Init(GPIOC, 0, GpioPin::Type::AlternateFunction, 10, GpioPin::DriveStrength::VeryHigh);	// PC0  OCTOSPI_IO7 AF10
	GpioPin::Init(GPIOB, 10, GpioPin::Type::AlternateFunction, 9, GpioPin::DriveStrength::VeryHigh);	// PB10 OCTOSPI_NCS AF10
	GpioPin::Init(GPIOB, 2, GpioPin::Type::AlternateFunction, 10, GpioPin::DriveStrength::VeryHigh);	// PB2  OCTOSPI_DQS AF10

	RCC->AHB4ENR |= RCC_AHB4ENR_OCTOSPI1EN;
	//RCC->CCIPR4 &= ~RCC_CCIPR4_OCTOSPISEL;					// kernel clock 250MHz: 00 rcc_hclk4 (default); 01 pll1_q_ck; 10 pll2_r_ck; 11 per_ck
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
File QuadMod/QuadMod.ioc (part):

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Mcu.Name=STM32H563VITx
Mcu.Package=LQFP100
Mcu.UserName=STM32H563VITx
PA0.Signal=ADCx_INP0
PA1.Signal=ADCx_INP1
PA2.Signal=ADCx_INP14
PA4.Mode=NSS_Signal_Hard_Output
PA4.Signal=SPI1_NSS
PA5.Mode=Full_Duplex_Master
PA5.Signal=SPI1_SCK
PA6.Signal=ADCx_INP3
PA7.Signal=ADCx_INP7
PB0.Signal=SharedAnalog_PB0
PB4(NJTRST).Mode=Full_Duplex_Master
PB4(NJTRST).Signal=SPI1_MISO
PB5.Mode=Full_Duplex_Master
PB5.Signal=SPI1_MOSI
PC1.Signal=ADCx_INP11
PC4.Signal=ADCx_INP4
PC5.Signal=ADCx_INP8
PE2.Mode=SAI_A_MasterWithClock
PE2.Signal=SAI1_MCLK_A
PE4.Mode=SAI_A_MasterWithClock
PE4.Signal=SAI1_FS_A
PE5.Mode=SAI_A_MasterWithClock
PE5.Signal=SAI1_SCK_A
PE6.Mode=SAI_A_MasterWithClock
PE6.Signal=SAI1_SD_A
PH0-OSC_IN(PH0).Mode=HSE-External-Oscillator
PH0-OSC_IN(PH0).Signal=RCC_OSC_IN
PH1-OSC_OUT(PH1).Mode=HSE-External-Oscillator
PH1-OSC_OUT(PH1).Signal=RCC_OSC_OUT
RCC.HSE_VALUE=12000000
RCC.SYSCLKFreq_VALUE=250000000
RCC.SYSCLKSource=RCC_SYSCLKSOURCE_PLLCLK
board=custom

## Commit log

2023-07-27 Started configuring SAI peripheral
2023-07-28 Updated SAI clock generation
2023-07-28 SAI1 correctly outputting 32 bit I2S test pattern
2023-07-28 SAI now sending and receiving I2S data over loop-back
2023-07-28 Started configuring SAI2
2023-07-29 SAI2 A receiving I2S data in loopback from SAI1A
2023-07-29 SAI working as dual transmitter on SAI1 and dual receiver on SAI2
2023-07-29 Started adding USB functionality
2023-07-30 USB class compiles without errors
2023-07-31 USB enumeration working
2023-07-31 USB CDC working
2023-08-01 Cleaned up USB code
2023-08-01 Started laying out Audio Codec Test Board
2023-08-02 Added HyperRam to Dev Board
2023-08-04 Added Input scaling
2023-08-23 Added Ouput op-amp
2023-08-23 DevBoard Gerbers ordered
2023-09-14 Comment changes
2023-11-01 Updated USB classes
2023-11-02 Fixed issue getting UID in USB setup routine (using MPU)
2023-11-02 Implemented SPI to control Audio Codec
2023-11-02 Fixed SPI data send; trying to read back register
2023-11-03 Audio codec SPI initialisation and read/write tested working
2023-11-03 DAC output seems to be working
2023-11-03 Created signals to test DAC outputs
2023-11-04 Updated SAI FIFO interrupt to prevent underruns
    Test output sine wave
2023-11-04 Audio recording working on channel 1 (fixed I2S input clock polarity)
2023-11-05 Changed I2S implementation so that output and input signals are sampled on rising edge
2023-11-05 Cleaned up Audio Codec test signal loop-back
2023-11-05 Changed codec ADC filter to improve latency
    Also added serial support for writing to codec registers
2023-11-05 removed comment
2023-11-06 Created a GpioPin class to manage GPIO initialisation and setting
2023-11-06 Started configuring HyperRAM
2023-11-08 Configured HyperRAM to (apparently) read register values
2023-11-08 Started adding hyperRAM write mode
2023-11-09 Fixed crash after writing; data still not being written, however
2023-11-10 Writing is doing something, but written data offset
    Also prescaler changes alter read/write patterns
2023-11-10 Added drive strength to GPIO header
2023-12-04 Continued unsuccessful attempts to get HyperRAM working
2023-12-06 Started implementing delay code
2023-12-06 Very simple quad delay test working
2023-12-08 Basic stereo ripple effect working
2023-12-09 Started configuring ADC DMA
2023-12-09 ADC with DMA seems to be working
    Using DMA Linked list to update registers
2023-12-09 Cleaned up ADC/DMA initialisation
2023-12-10 Implemented cross-fading delay time changing
2023-12-10 Added tanh limiting to sample output
2023-12-10 Added ADC controlled LP filter to delay
2023-12-11 Started adding phaser code
2023-12-15 Working on USB failing under optimise level O1
2023-12-15 Work on optimising phaser filter calculations
2023-12-17 Phaser improvements; added cordic function
2023-12-17 Implemented Cordic trig functions in phaser
2023-12-18 Started adding serial web editor
2023-12-19 Updates to web serial editor; cleaned signal path
2023-12-20 Fixes to web serial editor; mix levels for effects and delay
2023-12-20 Tweaking levels
2023-12-21 Reorganised delay samples for better cache locality
2023-12-21 Code optimisation and clean up
2023-12-21 Started adding framework for flanger code
2023-12-24 Updated flanger code to include feedback
2023-12-24 Added configurable flanger baseFrequency
2024-01-06 Web editor range pickers built automatically
2024-01-16 Moved effect sample buffer to effectManager class for shared access
2024-01-17 Basic octave down effect working in RingMod effect
2024-01-17 RingMod octave down now LP filtered
2024-01-18 Added switch to change between octave/ringmod; Updated web editor for dynamic check boxes
2024-01-18 Started adding clocked delay
2024-01-20 Clocked delay working; fixes to flanger
2024-01-20 Fixed buffer overrun in flanger
2024-01-21 Phaser filter count can be set to any number between 1 and 16
2024-01-21 Implemented constant power effect/delay mix controls
2024-01-22 Fixed bug in flanger sample interpolation
2024-01-22 Added wide option to flanger
2024-01-23 Started roughing out panel design
2024-01-25 Work on panel
2024-01-25 Updates to Panel
2024-01-26 First draft of panel completed
2024-01-27 Cleaned up schematic
2024-01-27 Started component layout
2024-01-28 Preliminary component routing
2024-01-29 First pass signal routing of component board
2024-01-30 First draft of power routing completed
2024-01-30 Basic layout complete
2024-01-31 First draft of control board
2024-01-31 Started adding additional clock LED
2024-02-01 Clean up of schematics and PCBS
2024-02-02 Draft Gerber Creation
2024-02-04 Updated Production Gerbers; attempts to get USB working with O1 optimisation
2024-03-03 Pre-bring up backup
2024-03-03 Configured and tested clock and adc
2024-03-03 USB and Audio Codec SPI working
2024-03-03 Audio codec output tested and working
2024-03-03 Audio channels 3 and 4 working; Added LED PWM
2024-03-04 All codec inputs tested after board rework on PC1
2024-03-05 Updated GpioPIn.h; basic delay LED working
2024-03-06 Implemented effect switching
2024-03-06 Phaser displays modulation LFO on LED
2024-03-06 Refactored ADC mappings
2024-03-07 Code cleanup; started dubugging crackles on flanger
2024-03-07 Added flanger ADC smoothing
2024-03-07 ADC smoothing; Delay LED fades out
2024-03-07 Started improving delay clock detection
2024-03-08 Code cleanup
2024-03-09 Added readme
